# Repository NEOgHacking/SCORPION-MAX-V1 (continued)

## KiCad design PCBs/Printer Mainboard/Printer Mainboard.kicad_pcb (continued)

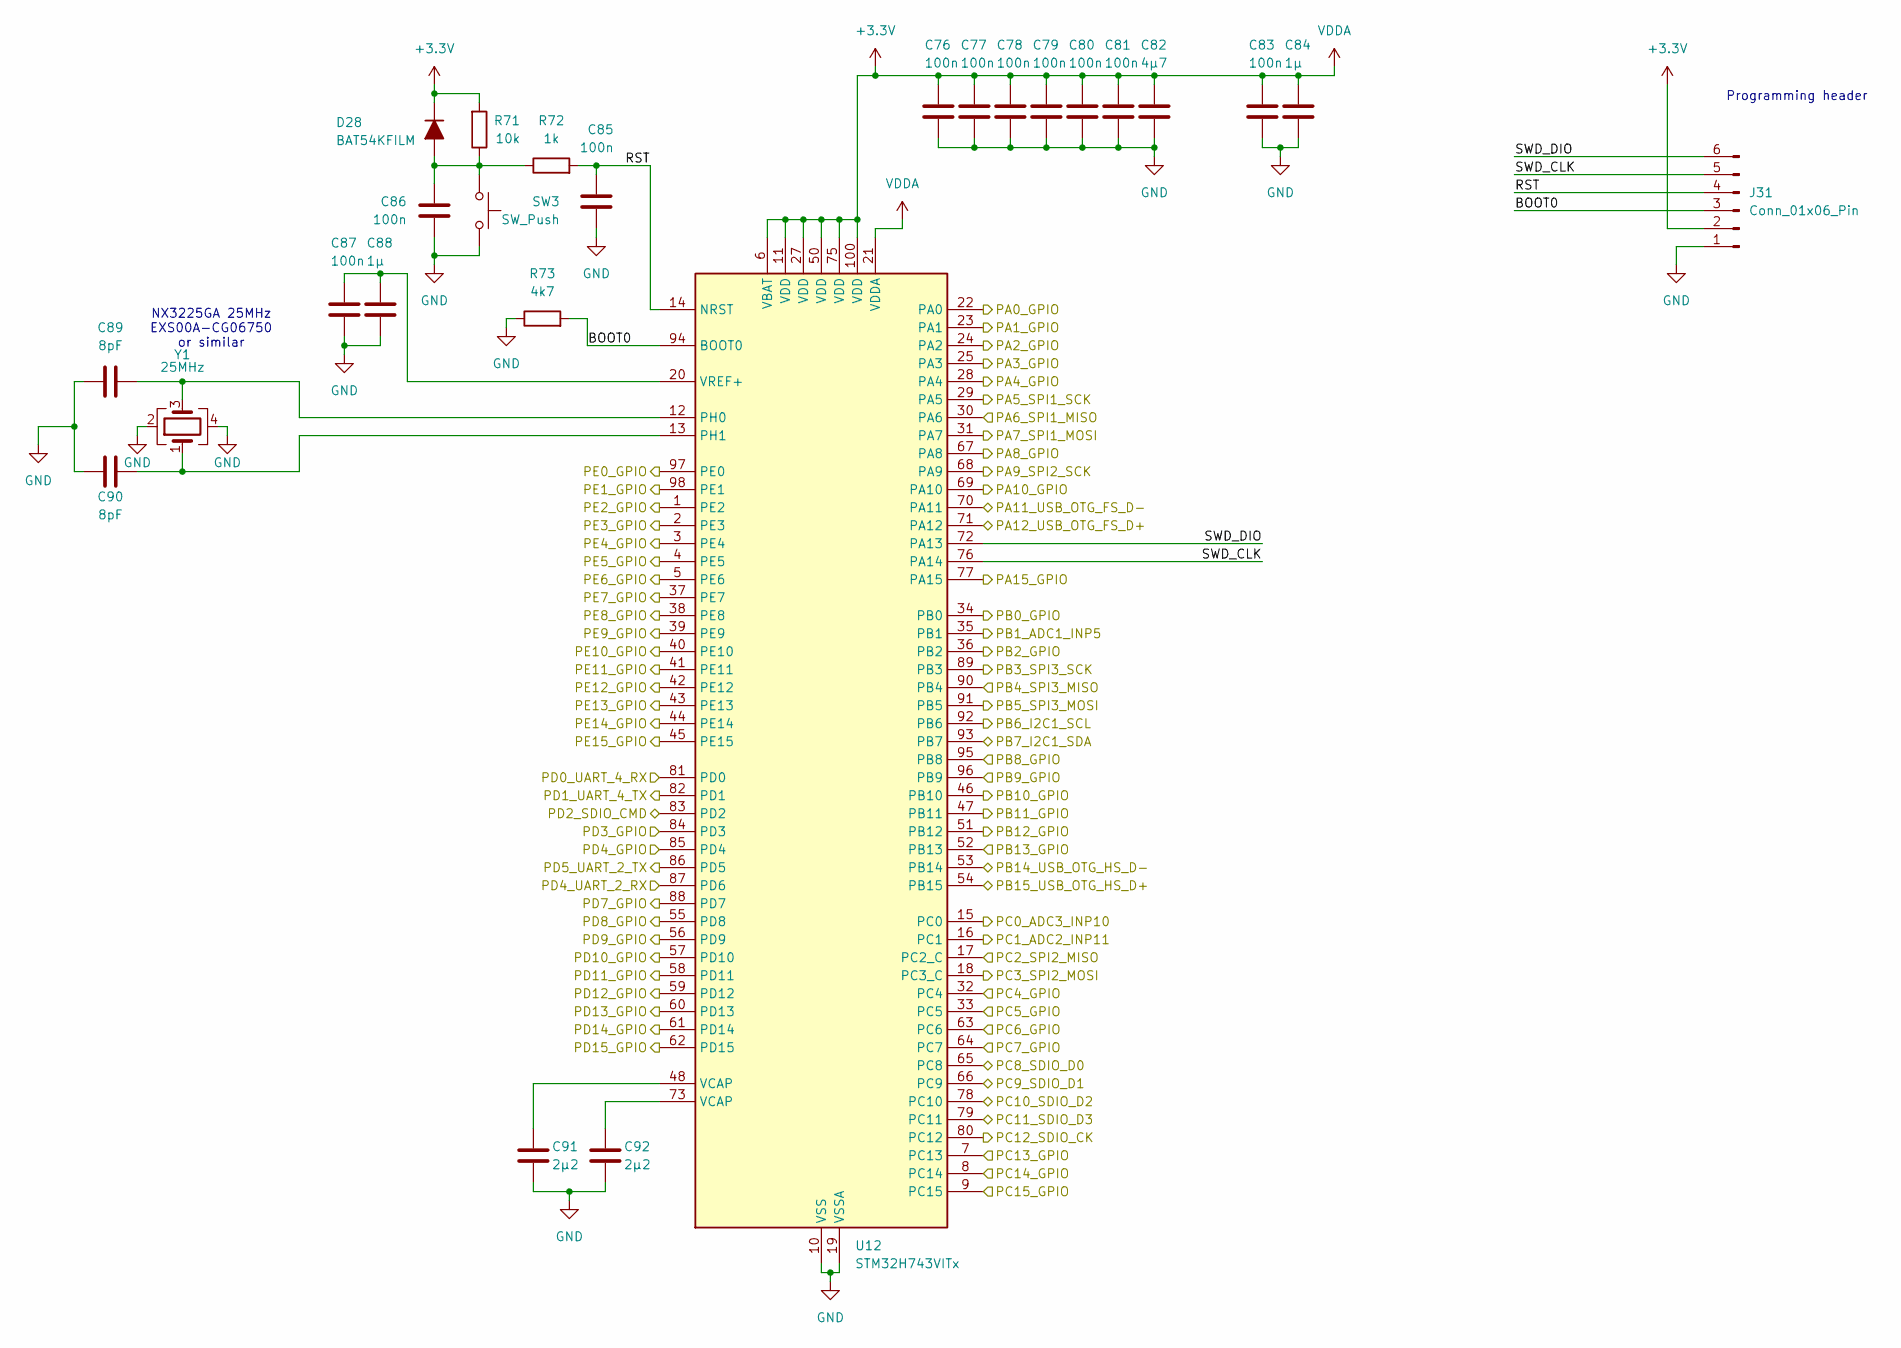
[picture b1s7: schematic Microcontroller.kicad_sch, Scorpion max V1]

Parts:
C76, C77, C78, C79, C80, C81, C83, C85, C86, C87: 100n; C_0603_1608Metric
C82: 4μ7; C_0805_2012Metric
C84, C88: 1μ; C_0603_1608Metric
C89, C90: 8pF; C_0603_1608Metric
C91, C92: 2μ2; C_0603_1608Metric
D28: BAT54KFILM; D_SOD-523
J31: Conn_01x06_Pin; PinHeader_1x06_P2.54mm_Vertical
R71: 10k; R_0603_1608Metric
R72: 1k; R_0603_1608Metric
R73: 4k7; R_0603_1608Metric
SW3: SW_Push; B3F3120
U12: STM32H743VITx; LQFP-100_14x14mm_P0.5mm
Y1: 25MHz; Crystal_SMD_3225-4Pin_3.2x2.5mm

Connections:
+3.3V: C76.1, C77.1, C78.1, C79.1, C80.1, C81.1, C82.1, C83.1, C84.1, D28.1 (K), J31.2, R71.2, U12.6 (VBAT), U12.11 (VDD), U12.21 (VDDA), U12.27 (VDD), U12.50 (VDD), U12.75 (VDD), U12.100 (VDD); also elsewhere on the board
/Expansion Port/GPIO_1: U12.5 (PE6); also elsewhere on the board
/Expansion Port/GPIO_2: U12.4 (PE5); also elsewhere on the board
/Expansion Port/GPIO_3: U12.3 (PE4); also elsewhere on the board
/Expansion Port/GPIO_4: U12.2 (PE3); also elsewhere on the board
/Expansion Port/GPIO_5: U12.1 (PE2); also elsewhere on the board
/Expansion Port/GPIO_6: U12.98 (PE1); also elsewhere on the board
/Expansion Port/GPIO_7: U12.97 (PE0); also elsewhere on the board
/Expansion Port/GPIO_8: U12.96 (PB9); also elsewhere on the board
/Expansion Port/GPIO_9: U12.84 (PD3); also elsewhere on the board
/Expansion Port/GPIO_10: U12.85 (PD4); also elsewhere on the board
/Expansion Port/GPIO_11: U12.88 (PD7); also elsewhere on the board
/Expansion Port/GPIO_12: U12.95 (PB8); also elsewhere on the board
/Expansion Port/RXD1: U12.81 (PD0); also elsewhere on the board
/Expansion Port/RXD2: U12.87 (PD6); also elsewhere on the board
/Expansion Port/SCL: U12.92 (PB6); also elsewhere on the board
/Expansion Port/SDA: U12.93 (PB7); also elsewhere on the board
/Expansion Port/SDIO_CK: U12.80 (PC12); also elsewhere on the board
/Expansion Port/SDIO_CMD: U12.83 (PD2); also elsewhere on the board
/Expansion Port/SDIO_D0: U12.65 (PC8); also elsewhere on the board
/Expansion Port/SDIO_D1: U12.66 (PC9); also elsewhere on the board
/Expansion Port/SDIO_D2: U12.78 (PC10); also elsewhere on the board
/Expansion Port/SDIO_D3: U12.79 (PC11); also elsewhere on the board
/Expansion Port/SPI_MISO: U12.90 (PB4); also elsewhere on the board
/Expansion Port/SPI_MOSI: U12.91 (PB5); also elsewhere on the board
/Expansion Port/SPI_SCK: U12.89 (PB3); also elsewhere on the board
/Expansion Port/TXD1: U12.82 (PD1); also elsewhere on the board
/Expansion Port/TXD2: U12.86 (PD5); also elsewhere on the board
/Fans Leds/FAN_1_PIN: U12.55 (PD8); also elsewhere on the board
/Fans Leds/FAN_1_TACH: U12.56 (PD9); also elsewhere on the board
/Fans Leds/FAN_2_PIN: U12.47 (PB11); also elsewhere on the board
/Fans Leds/FAN_2_TACH: U12.57 (PD10); also elsewhere on the board
/Fans Leds/FAN_3_PIN: U12.46 (PB10); also elsewhere on the board
/Fans Leds/FAN_3_TACH: U12.58 (PD11); also elsewhere on the board
/Fans Leds/FAN_4_PIN: U12.45 (PE15); also elsewhere on the board
/Fans Leds/FAN_4_TACH: U12.59 (PD12); also elsewhere on the board
/Limit Switches/LIMIT_1_PIN: U12.77 (PA15); also elsewhere on the board
/Limit Switches/LIMIT_2_PIN: U12.69 (PA10); also elsewhere on the board
/Limit Switches/LIMIT_3_PIN: U12.67 (PA8); also elsewhere on the board
/Limit Switches/LIMIT_4_PIN: U12.64 (PC7); also elsewhere on the board
/MOSFETS/MOSFET_1_PIN: U12.63 (PC6); also elsewhere on the board
/MOSFETS/MOSFET_2_PIN: U12.62 (PD15); also elsewhere on the board
/MOSFETS/MOSFET_3_PIN: U12.61 (PD14); also elsewhere on the board
/MOSFETS/MOSFET_4_PIN: U12.60 (PD13); also elsewhere on the board
/Microcontroller/BOOT0: J31.3, R73.2, U12.94 (BOOT0)
/Microcontroller/PA0_GPIO: U12.22 (PA0); also elsewhere on the board
/Microcontroller/PA1_GPIO: U12.23 (PA1); also elsewhere on the board
/Microcontroller/PA2_GPIO: U12.24 (PA2); also elsewhere on the board
/Microcontroller/PA3_GPIO: U12.25 (PA3); also elsewhere on the board
/Microcontroller/PA4_GPIO: U12.28 (PA4); also elsewhere on the board
/Microcontroller/PA5_SPI1_SCK: U12.29 (PA5); also elsewhere on the board
/Microcontroller/PA6_SPI1_MISO: U12.30 (PA6); also elsewhere on the board
/Microcontroller/PA7_SPI1_MOSI: U12.31 (PA7); also elsewhere on the board
/Microcontroller/PA9_SPI2_SCK: U12.68 (PA9); also elsewhere on the board
/Microcontroller/PB0_GPIO: U12.34 (PB0); also elsewhere on the board
/Microcontroller/PB1_ADC1_INP5: U12.35 (PB1); also elsewhere on the board
/Microcontroller/PB2_GPIO: U12.36 (PB2); also elsewhere on the board
/Microcontroller/PB12_GPIO: U12.51 (PB12); also elsewhere on the board
/Microcontroller/PB13_GPIO: U12.52 (PB13); also elsewhere on the board
/Microcontroller/PC0_ADC3_INP10: U12.15 (PC0); also elsewhere on the board
/Microcontroller/PC1_ADC2_INP11: U12.16 (PC1); also elsewhere on the board
/Microcontroller/PC2_SPI2_MISO: U12.17 (PC2_C); also elsewhere on the board
/Microcontroller/PC3_SPI2_MOSI: U12.18 (PC3_C); also elsewhere on the board
/Microcontroller/PC4_GPIO: U12.32 (PC4); also elsewhere on the board
/Microcontroller/PC5_GPIO: U12.33 (PC5); also elsewhere on the board
/Microcontroller/PC13_GPIO: U12.7 (PC13); also elsewhere on the board
/Microcontroller/PC14_GPIO: U12.8 (PC14); also elsewhere on the board
/Microcontroller/PC15_GPIO: U12.9 (PC15); also elsewhere on the board
/Microcontroller/PE7_GPIO: U12.37 (PE7); also elsewhere on the board
/Microcontroller/PE8_GPIO: U12.38 (PE8); also elsewhere on the board
/Microcontroller/PE9_GPIO: U12.39 (PE9); also elsewhere on the board
/Microcontroller/PE10_GPIO: U12.40 (PE10); also elsewhere on the board
/Microcontroller/PE11_GPIO: U12.41 (PE11); also elsewhere on the board
/Microcontroller/PE12_GPIO: U12.42 (PE12); also elsewhere on the board
/Microcontroller/PE13_GPIO: U12.43 (PE13); also elsewhere on the board
/Microcontroller/PE14_GPIO: U12.44 (PE14); also elsewhere on the board
/Microcontroller/RST: C85.1, J31.4, R72.2, U12.14 (NRST)
/Microcontroller/SWD_CLK: J31.5, U12.76 (PA14)
/Microcontroller/SWD_DIO: J31.6, U12.72 (PA13)
/USB/USB_A_D+: U12.54 (PB15); also elsewhere on the board
/USB/USB_A_D-: U12.53 (PB14); also elsewhere on the board
/USB/USB_C_D+: U12.71 (PA12); also elsewhere on the board
/USB/USB_C_D-: U12.70 (PA11); also elsewhere on the board
GND: C76.2, C77.2, C78.2, C79.2, C80.2, C81.2, C82.2, C83.2, C84.2, C85.2, C86.2, C87.2, C88.2, C89.1, C90.1, C91.2, C92.2, J31.1, R73.1, SW3.1, U12.10 (VSS), U12.19 (VSSA), U12.26 (VSS), U12.49 (VSS), U12.74 (VSS), U12.99 (VSS), Y1.2, Y1.4; also elsewhere on the board
unnamed: C91.1, U12.48 (VCAP)
unnamed: C92.1, U12.73 (VCAP)
unnamed: C86.1, D28.2 (A), R71.1, R72.1, SW3.2
unnamed: C89.2, U12.12 (PH0), Y1.3
unnamed: C90.2, U12.13 (PH1), Y1.1
unnamed: C87.1, C88.1, U12.20 (VREF+)

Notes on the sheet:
Programming header
NX3225GA 25MHz EXS00A-CG06750 or similar

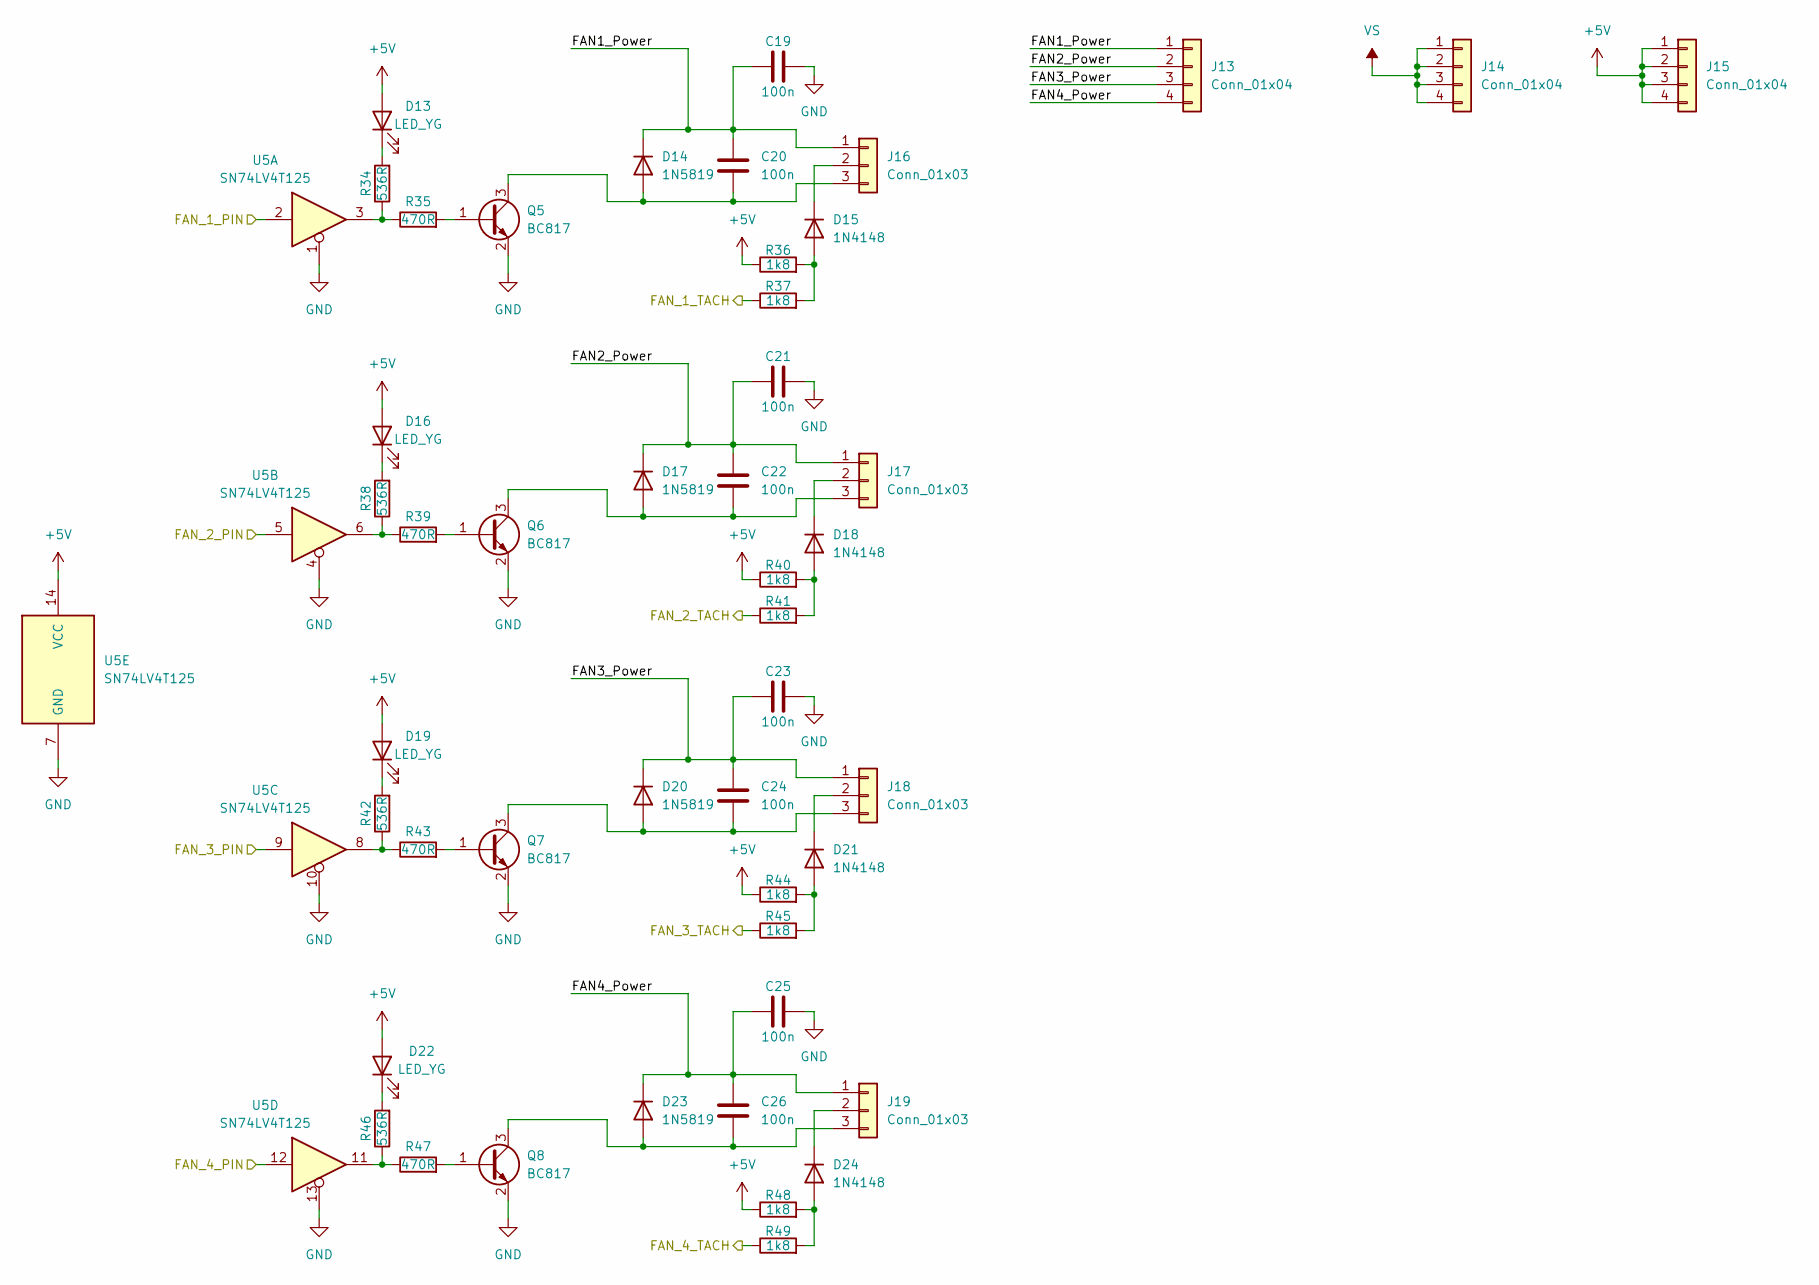
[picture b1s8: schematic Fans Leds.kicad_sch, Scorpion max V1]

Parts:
C19, C20, C21, C22, C23, C24, C25, C26: 100n; C_0603_1608Metric
D13, D16, D19, D22: LED_YG; LED_0603_1608Metric
D14, D17, D20, D23: 1N5819; D_SOD-323
D15, D18, D21, D24: 1N4148; D_SOD-523
J13, J14, J15: Conn_01x04; PinSocket_1x04_P2.54mm_Vertical
J16, J17, J18, J19: Conn_01x03; JST_XH_B3B-XH-A_1x03_P2.50mm_Vertical
Q5, Q6, Q7, Q8: BC817; SOT-23
R34, R38, R42, R46: 536R; R_0603_1608Metric
R35, R39, R43, R47: 470R; R_0603_1608Metric
R36, R37, R40, R41, R44, R45, R48, R49: 1k8; R_0603_1608Metric
U5: SN74LV4T125; TSSOP-14_4.4x5mm_P0.65mm

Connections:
+5V: D13.2 (A), D16.2 (A), D19.2 (A), D22.2 (A), J15.1, J15.2, J15.3, J15.4, R36.1, R40.1, R44.1, R48.1, U5.14 (VCC); also elsewhere on the board
/Fans Leds/FAN1_Power: C19.1, C20.1, D14.1 (K), J13.1, J16.1
/Fans Leds/FAN2_Power: C21.1, C22.1, D17.1 (K), J13.2, J17.1
/Fans Leds/FAN3_Power: C23.1, C24.1, D20.1 (K), J13.3, J18.1
/Fans Leds/FAN4_Power: C25.1, C26.1, D23.1 (K), J13.4, J19.1
/Fans Leds/FAN_1_PIN: U5.2; also elsewhere on the board
/Fans Leds/FAN_1_TACH: R37.1; also elsewhere on the board
/Fans Leds/FAN_2_PIN: U5.5; also elsewhere on the board
/Fans Leds/FAN_2_TACH: R41.1; also elsewhere on the board
/Fans Leds/FAN_3_PIN: U5.9; also elsewhere on the board
/Fans Leds/FAN_3_TACH: R45.1; also elsewhere on the board
/Fans Leds/FAN_4_PIN: U5.12; also elsewhere on the board
/Fans Leds/FAN_4_TACH: R49.1; also elsewhere on the board
GND: C19.2, C21.2, C23.2, C25.2, Q5.2 (E), Q6.2 (E), Q7.2 (E), Q8.2 (E), U5.1, U5.4, U5.7 (GND), U5.10, U5.13; also elsewhere on the board
unnamed: D13.1 (K), R34.2
unnamed: C20.2, D14.2 (A), J16.3, Q5.3 (C)
unnamed: D15.2 (A), R36.2, R37.2
unnamed: D15.1 (K), J16.2
unnamed: D16.1 (K), R38.2
unnamed: C22.2, D17.2 (A), J17.3, Q6.3 (C)
unnamed: D18.2 (A), R40.2, R41.2
unnamed: D18.1 (K), J17.2
unnamed: D19.1 (K), R42.2
unnamed: C24.2, D20.2 (A), J18.3, Q7.3 (C)
unnamed: D21.2 (A), R44.2, R45.2
unnamed: D21.1 (K), J18.2
unnamed: D22.1 (K), R46.2
unnamed: C26.2, D23.2 (A), J19.3, Q8.3 (C)
unnamed: D24.2 (A), R48.2, R49.2
unnamed: D24.1 (K), J19.2
unnamed: Q5.1 (B), R35.2
unnamed: Q6.1 (B), R39.2
unnamed: Q7.1 (B), R43.2
unnamed: Q8.1 (B), R47.2
unnamed: R34.1, R35.1, U5.3
unnamed: R38.1, R39.1, U5.6
unnamed: R42.1, R43.1, U5.8
unnamed: R46.1, R47.1, U5.11
VS: J14.1, J14.2, J14.3, J14.4; also elsewhere on the board

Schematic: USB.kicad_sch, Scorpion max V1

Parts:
C1: 100n; C_0603_1608Metric
C2: 4μ7; C_0805_2012Metric
D1: LED_R; LED_0603_1608Metric
D2: DSK24L; D_SOD-123F
J1: USB_A; USB-A-TH_USB-302-T
J2: USB_C_Receptacle_USB2.0_14P; USB-C_SMD-TYPE-C-31-M-12_1
R1: 47k; R_0603_1608Metric
R2: 620R; R_0603_1608Metric
R3, R4: 5k1; R_0603_1608Metric
S1: STMPS2141STR; SOT95P280X145-5N; Mouser Part Number 511-STMPS2141STR
U1: USBLC6-2SC6; SOT-23-6

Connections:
+5V: D2.1 (K), R1.1, R2.1, S1.5 (IN); also elsewhere on the board
/Microcontroller/PB12_GPIO: S1.4 (EN); also elsewhere on the board
/Microcontroller/PB13_GPIO: D1.1 (K), R1.2, S1.3 (FAULT); also elsewhere on the board
/USB/USB_A_D+: U1.1 (I/O1); also elsewhere on the board
/USB/USB_A_D-: U1.3 (I/O2); also elsewhere on the board
/USB/USB_A_VBUS: C1.1, C2.1, J1.1 (VBUS), S1.1 (OUT), U1.5 (VBUS)
/USB/USB_C_D+: J2.A6 (D+), J2.B6 (D+); also elsewhere on the board
/USB/USB_C_D-: J2.A7 (D-), J2.B7 (D-); also elsewhere on the board
GND: C1.2, C2.2, J1.4 (GND), J1.5 (Shield), J2.A1B12 (GND), J2.B1A12 (GND), J2.S1 (SHIELD), R3.2, R4.2, S1.2 (GND), U1.2 (GND); also elsewhere on the board
unnamed: D1.2 (A), R2.2
unnamed: D2.2 (A), J2.A4B9 (VBUS), J2.B4A9 (VBUS)
unnamed: J1.3 (D+), U1.6 (I/O1)
unnamed: J1.2 (D-), U1.4 (I/O2)
unnamed: J2.A5 (CC1), R3.1
unnamed: J2.B5 (CC2), R4.1

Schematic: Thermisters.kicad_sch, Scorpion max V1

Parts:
C93, C94, C95: 100n; C_0603_1608Metric
J32, J35, J38: Conn_01x03; PinSocket_1x03_P2.54mm_Vertical
J33, J36, J39: Conn_01x02; JST_XH_B2B-XH-A_1x02_P2.50mm_Vertical
J34, J37, J40: Conn_01x02; PinSocket_1x02_P2.54mm_Vertical

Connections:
+3.3V: J32.3, J35.3, J38.3; also elsewhere on the board
/Microcontroller/PB1_ADC1_INP5: C93.1, J32.2; also elsewhere on the board
/Microcontroller/PC0_ADC3_INP10: C95.1, J38.2; also elsewhere on the board
/Microcontroller/PC1_ADC2_INP11: C94.1, J35.2; also elsewhere on the board
GND: C93.2, C94.2, C95.2, J32.1, J35.1, J38.1; also elsewhere on the board
unnamed: J33.1, J34.1
unnamed: J33.2, J34.2
unnamed: J36.1, J37.1
unnamed: J36.2, J37.2
unnamed: J39.1, J40.1
unnamed: J39.2, J40.2

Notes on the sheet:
Thermister
Temp Module

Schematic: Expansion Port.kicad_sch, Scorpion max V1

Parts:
J11, J12: Conn_02x08_Odd_Even; PinSocket_2x08_P2.54mm_Vertical

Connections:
+3.3V: J11.14; also elsewhere on the board
+5V: J11.16, J12.16; also elsewhere on the board
/Expansion Port/GPIO_1: J12.1; also elsewhere on the board
/Expansion Port/GPIO_2: J12.2; also elsewhere on the board
/Expansion Port/GPIO_3: J12.3; also elsewhere on the board
/Expansion Port/GPIO_4: J12.4; also elsewhere on the board
/Expansion Port/GPIO_5: J12.5; also elsewhere on the board
/Expansion Port/GPIO_6: J12.6; also elsewhere on the board
/Expansion Port/GPIO_7: J12.7; also elsewhere on the board
/Expansion Port/GPIO_8: J12.8; also elsewhere on the board
/Expansion Port/GPIO_9: J12.9; also elsewhere on the board
/Expansion Port/GPIO_10: J12.10; also elsewhere on the board
/Expansion Port/GPIO_11: J12.11; also elsewhere on the board
/Expansion Port/GPIO_12: J12.12; also elsewhere on the board
/Expansion Port/RXD1: J11.6; also elsewhere on the board
/Expansion Port/RXD2: J11.10; also elsewhere on the board
/Expansion Port/SCL: J12.14; also elsewhere on the board
/Expansion Port/SDA: J12.13; also elsewhere on the board
/Expansion Port/SDIO_CK: J11.5; also elsewhere on the board
/Expansion Port/SDIO_CMD: J11.8; also elsewhere on the board
/Expansion Port/SDIO_D0: J11.1; also elsewhere on the board
/Expansion Port/SDIO_D1: J11.2; also elsewhere on the board
/Expansion Port/SDIO_D2: J11.3; also elsewhere on the board
/Expansion Port/SDIO_D3: J11.4; also elsewhere on the board
/Expansion Port/SPI_MISO: J11.12; also elsewhere on the board
/Expansion Port/SPI_MOSI: J11.13; also elsewhere on the board
/Expansion Port/SPI_SCK: J11.11; also elsewhere on the board
/Expansion Port/TXD1: J11.7; also elsewhere on the board
/Expansion Port/TXD2: J11.9; also elsewhere on the board
GND: J11.15, J12.15; also elsewhere on the board

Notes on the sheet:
Expansion Module

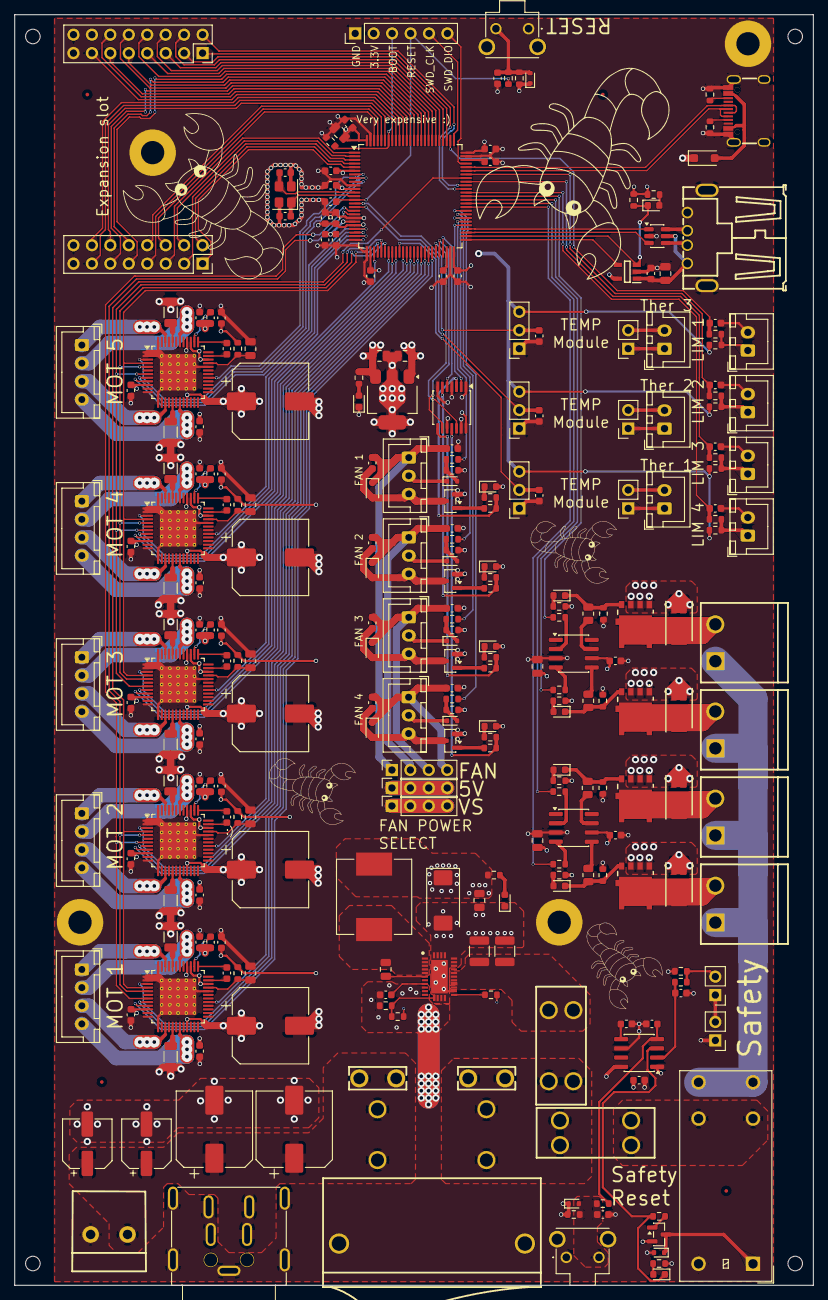
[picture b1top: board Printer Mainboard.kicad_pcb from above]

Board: 4 copper layers, 110.0 x 175.0 mm, 279 parts (0 on the bottom side), 228 nets.

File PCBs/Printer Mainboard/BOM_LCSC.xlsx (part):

Reference | Qty | Value | DNP | Exclude from BOM | Exclude from Board | Footprint | Part | component | LCSC number | Qty 2x Boards | Order | Total Price | Do Not Order | Extra
C1,C11,C12,C13,C14,C16,C18,C19,C20,C21,C22,C23,C24,C25,C26,C31,C32,C33,C34,C46,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 | 52 | 100n | 1 |  |  | Capacitor_SMD:C_0603_1608Metric | Capacitor 100n 50V | CC0603KRX7R9BB104 | C14663 | 104 | 200 | 0.44 |  |  |  |  |  |  |  |  |  |  |  |  | Vin | Vmin | Vmax | Vavg. | mA | R
C2,C9,C10,C15,C17,C41,C42,C43,C44,C45,C82 | 11 | 4Î¼7 | 2 |  |  | Capacitor_SMD:C_0805_2012Metric | Capacitor 4μ7 50V | CL21A475KBQNNNE | C98192 | 22 | 50 | 0.88 |  |  |  |  |  |  |  |  |  |  |  | Led Red | 3.3 | 1.6 | 2.1 | 1.85 | 5 | 289.99999999999994
C3,C5 | 2 | 470n 10V | 3 |  |  | Capacitor_SMD:C_0805_2012Metric | Capacitor 470n 10V | VJ0805Y474KXQTW1BC | C2177586 | 4 | 5 | 0.26 |  |  |  |  |  |  |  |  |  |  |  | Led Blue | 3.3 | 2.6 | 3.2 | 2.9000000000000004 | 5 | 79.999999999999886
C4 | 1 | 220Î¼ 10V | 4 |  |  | Capacitor_Tantalum_SMD:CP_EIA-7343-43_Kemet-X | Capacitor 220μ 10V | 593D227X0010E2TE3 | C1952898 | 2 | 2 | 0.85 |  |  |  |  |  |  |  |  |  |  |  | Led Green | 3.3 | 2.4 | 3 | 2.7 | 5 | 119.99999999999993
C6 | 1 | 470n 100V | 5 |  |  | Capacitor_SMD:C_1210_3225Metric | Capacitor 470n 100V | VJ1210Y474KXBAT | C2313088 | 2 | 3 | 1.28 |  |  |  |  |  |  |  |  |  |  |  | Led Yellow Green | 3.3 | 2.2999999999999998 | 2.2999999999999998 | 2.2999999999999998 | 5 | 200
C7 | 1 | 4Î¼7 100V | 6 |  |  | Capacitor_SMD:C_1210_3225Metric | Capacitor 4μ7 100V | C3225X7S2A475KT003S | C694475 | 2 | 5 | 1.97 |  |  |  |  |  |  |  |  |  |  |  | Led Red | 5 | 1.6 | 2.1 | 1.85 | 5 | 630
C8 | 1 | 2Î¼2 16V | 7 |  |  | Capacitor_SMD:C_0603_1608Metric | Capacitor 2μ2 16V | C1608X5R1C225KT000N | C76612 | 2 | 5 | 0.16 |  |  |  |  |  |  |  |  |  |  |  | Led Blue | 5 | 2.6 | 3.2 | 2.9000000000000004 | 5 | 419.99999999999994
C27,C28,C48,C51,C54,C57,C60 | 7 | 100Î¼ | 8 |  |  | Capacitor_SMD:CP_Elec_10x10 | Capacitor 100μ 63V | RVT1J101M1010 | C72481 | 14 | 20 | 1.75 |  |  |  |  |  |  |  |  |  |  |  | Led Green | 5 | 2.4 | 3 | 2.7 | 5 | 459.99999999999994
C29,C30 | 2 | 10Î¼ | 9 |  |  | Capacitor_SMD:CP_Elec_6.3x5.8 | Capacitor 10μ 63V | EEEFK1J100P | C128459 | 4 | 5 | 0.64 |  |  |  |  |  |  |  |  |  |  |  | Led Yellow Green | 5 | 2.2999999999999998 | 2.2999999999999998 | 2.2999999999999998 | 5 | 540
C35 | 1 | 10n | 10 |  |  | Capacitor_SMD:C_0603_1608Metric | Capacitor 10n 50V | CC0603KRX7R9BB103 | C100042 | 2 | 100 | 0.2
C36,C37,C38,C39,C40 | 5 | 470n | 11 |  |  | Capacitor_SMD:C_0603_1608Metric | Capacitor 470n 50V | CC0603KRX7R9BB474 | C513577 | 10 | 50 | 0.38
C71,C72,C73,C74,C75 | 5 | 22n | 12 |  |  | Capacitor_SMD:C_0603_1608Metric | Capacitor 22n 50V | CC0603KRX7R9BB223 | C106222 | 10 | 100 | 0.27
C84,C88 | 2 | 1Î¼ | 13 |  |  | Capacitor_SMD:C_0603_1608Metric | Capacitor 1μ 50V | CL10A105KB8NNNC | C15849 | 4 | 50 | 0.22
C89,C90 | 2 | 8pF | 14 |  |  | Capacitor_SMD:C_0603_1608Metric | Capacitor 8p 50V | CL10C080DB81PNC | C346204 | 4 | 50 | 0.44
C91,C92 | 2 | 2Î¼2 | 15 |  |  | Capacitor_SMD:C_0603_1608Metric | Capacitor 2μ2 50V | CL10A225KB8NNNC | C913904 | 4 | 50 | 0.96
D1,D26 | 2 | LED_R | 16 |  |  | LED_SMD:LED_0603_1608Metric | Led Red | A-SP192XR5C-A01-4T | C19171307 | 4 | 20 | 0.38
D2 | 1 | DSK24L | 17 |  |  | Diode_SMD:D_SOD-123F | Diode Low Forward Voltage | DSK24L | C19272974 | 2 | 10 | 0.5
D3,D4 | 2 | LED_G | 18 |  |  | LED_SMD:LED_0603_1608Metric | Led Green | A-SP192DGHC-C01-4T | C19171301 | 4 | 20 | 0.56000000000000005
D5,D7,D9,D11 | 4 | SMBJ64A | 19 |  |  | SamacSys_Parts:DIOM5436X250N | Diode Clamp | SMBJ64A | C19077594 | 8 | 10 | 0.4
D6,D8,D10,D12 | 4 | LED_B | 20 |  |  | LED_SMD:LED_0603_1608Metric | Led Blue | A-SP192DB1C-C01-4T | C5355419 | 8 | 20 | 0.44
D13,D16,D19,D22 | 4 | LED_YG | 21 |  |  | LED_SMD:LED_0603_1608Metric | Led Yellow Green | A-SP192DG2C-C01-4T | C5151486 | 8 | 20 | 0.56999999999999995
D14,D17,D20,D23 | 4 | 1N5819 | 22 |  |  | Diode_SMD:D_SOD-323 | Diode Schottky | 1N5819WS | C191023 | 8 | 50 | 0.47
D15,D18,D21,D24,D27 | 5 | 1N4148 | 23 |  |  | Diode_SMD:D_SOD-523 | Diode | 1N4148WT | C917006 | 10 | 100 | 0.44
D25,D28 | 2 | BAT54KFILM | 24 |  |  | Diode_SMD:D_SOD-523 | Diode Schottky | BAT54KFILM | C283259 | 4 | 10 | 0.5
F1,F2 | 2 | XF-508P-B-B | 25 |  |  | LCSC:FUSE-TH_4P-L16.0-W6.7 | Fuse Holder | XF-508P-B-B | C19727305 | 4 | 5 | 0.59
IC1 | 1 | LM76005RNPR | 26 |  |  | SamacSys_Parts:QFN50P400X600X80-31N-D | DC/DC Converter IC | LM76005QRNPRQ1 | C2873394 | 2 | 5 | 1
J1 | 1 | USB_A | 27 |  |  | LCSC:USB-A-TH_USB-302-T | USB_A | USB-302-T | C112456 | 2 | 2 | 9.7100000000000009
J2 | 1 | USB_C_Receptacle_USB2.0_14P | 28 |  |  | LCSC:USB-C_SMD-TYPE-C-31-M-12_1 | USB_C | TYPE-C-31-M-12 | C165948 | 2 | 5 | 0.77
J3,J4,J5,J6,J33,J36,J39 | 7 | Conn_01x02 | 29 |  |  | Connector_JST:JST_XH_B2B-XH-A_1x02_P2.50mm_Vertical | 2 Pin JST_XH | B2B-XH-A(LF)(SN) | C158012 | 14 | 20 | 0.61
J7,J8,J9,J10 | 4 | Conn_01x02 | 30 |  |  | LCSC:CONN-TH_2P-P5.08_2EDG-5.08-2AW | 2 Pin Header | 1923869 | C5443585 | 8 | 10 | 4.34 | x | I have these at home
J11,J12 | 2 | Conn_02x08_Odd_Even | 31 |  |  | Connector_PinSocket_2.54mm:PinSocket_2x08_P2.54mm_Vertical | 2x8 Pin Socket | PM2.54-2X8PM-H85 | C42431844 | 4 | 10 | 0.37
J13,J14,J15 | 3 | Conn_01x04 | 32 |  |  | Connector_PinSocket_2.54mm:PinSocket_1x04_P2.54mm_Vertical | 1x4 Pin Socket | PM2.54-1X4PM-H85 | C42431839 | 6 | 10 | 0.34
J16,J17,J18,J19 | 4 | Conn_01x03 | 33 |  |  | Connector_JST:JST_XH_B3B-XH-A_1x03_P2.50mm_Vertical | 3 Pin JST_XH | B3B-XH-A(LF)(SN) | C144394 | 8 | 10 | 0.41
J20,J21 | 2 | Faston | 34 |  |  | LCSC:CONN-TH_63849-1 | Faston | 63849-1 | C86469 | 4 | 10 | 0.54
J22 | 1 | Mini-DIN-4 | 35 |  |  | LCSC:CONN-TH_DIN-422 | 4 Pin Power In Connector | DIN-422 | C2939341 | 2 | 5 | 1.31
J23 | 1 | Conn_01x02 | 36 |  |  | LCSC:CONN-TH_MKDS3-2-5.08 | 2 Pin Screw Terminal | 1711725 | C89120 | 2 | 2 | 1.79
J24,J25 | 2 | Conn_01x02 | 37 |  |  | Connector_PinHeader_2.54mm:PinHeader_1x02_P2.54mm_Vertical | 1x2 Pin Header | PH2.54-1X2P-H25 | C42431798 | 4 | 50 | 0.33
J26,J27,J28,J29,J30 | 5 | Conn_01x04 | 38 |  |  | Connector_JST:JST_XH_B4B-XH-A_1x04_P2.50mm_Vertical | 4 Pin JST_XH | B4B-XH-A(LF)(SN) | C144395 | 10 | 20 | 0.89
J31 | 1 | Conn_01x06_Pin | 39 |  |  | Connector_PinHeader_2.54mm:PinHeader_1x06_P2.54mm_Vertical | 1x6 Pin Header | PZ2.54-1X6P-H25 | C42431790 | 2 | 20 | 0.25
J32,J35,J38 | 3 | Conn_01x03 | 40 |  |  | Connector_PinSocket_2.54mm:PinSocket_1x03_P2.54mm_Vertical | 1x3 Pin Socket | PM2.54-1X3P-H85 | C42431866 | 6 | 10 | 0.34
J34,J37,J40 | 3 | Conn_01x02 | 41 |  |  | Connector_PinSocket_2.54mm:PinSocket_1x02_P2.54mm_Vertical | 1x2 Pin Socket | PM2.54-1X2PM-H85 | C42431841 | 6 | 10 | 0.7
K1 | 1 | G2RL-1A-E | 42 |  |  | Relay_THT:Relay_SPST_Omron_G2RL-1A-E | Relay | G2RL-1A-E DC5 | C397259 | 2 | 2 | 2.73
L1 | 1 | 6.8Î¼ | 43 |  |  | Inductor_SMD:L_Vishay_IHLP-4040 | Inductor | IHLP4040DZER6R8M01 | C845080 | 2 | 2 | 1.66
Q1,Q2,Q3,Q4 | 4 | NVMFWS4D5N08XT1G | 44 |  |  | SamacSys_Parts:NVMFS5C460NWFT1G | Mosfet | NVMFWS4D5N08XT1G | C29841638 | 8 | 10 | 15.58
Q5,Q6,Q7,Q8 | 4 | BC817 | 45 |  |  | Package_TO_SOT_SMD:SOT-23 | Transistor NPN | BC817-40,215 | C52801 | 8 | 20 | 0.48
Q9 | 1 | BC807 | 46 |  |  | Package_TO_SOT_SMD:SOT-23 | Transistor PNP | BC807-40,215 | C57316 | 2 | 20 | 0.6
R1 | 1 | 47k | 47 |  |  | Resistor_SMD:R_0603_1608Metric | Resistor 47k | RC0603FR-0747KL | C105579 | 2 | 100 | 0.12
R2 | 1 | 620R | 48 |  |  | Resistor_SMD:R_0603_1608Metric | Resistor 620R | RC0603FR-07620RL | C137695 | 2 | 100 | 0.12
R3,R4 | 2 | 5k1 | 49 |  |  | Resistor_SMD:R_0603_1608Metric | Resistor 5k1 | RC0603FR-075K1L | C105580 | 4 | 100 | 0.13
R5 | 1 | 120R | 50 |  |  | Resistor_SMD:R_0603_1608Metric | Resisitor 120R | RC0603FR-07120RL | C114640 | 2 | 100 | 0.13
R6,R35,R39,R43,R47,R54 | 6 | 470R | 51 |  |  | Resistor_SMD:R_0603_1608Metric | Resistor 470R | RC0603FR-07470RL | C114669 | 12 | 100 | 0.13
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
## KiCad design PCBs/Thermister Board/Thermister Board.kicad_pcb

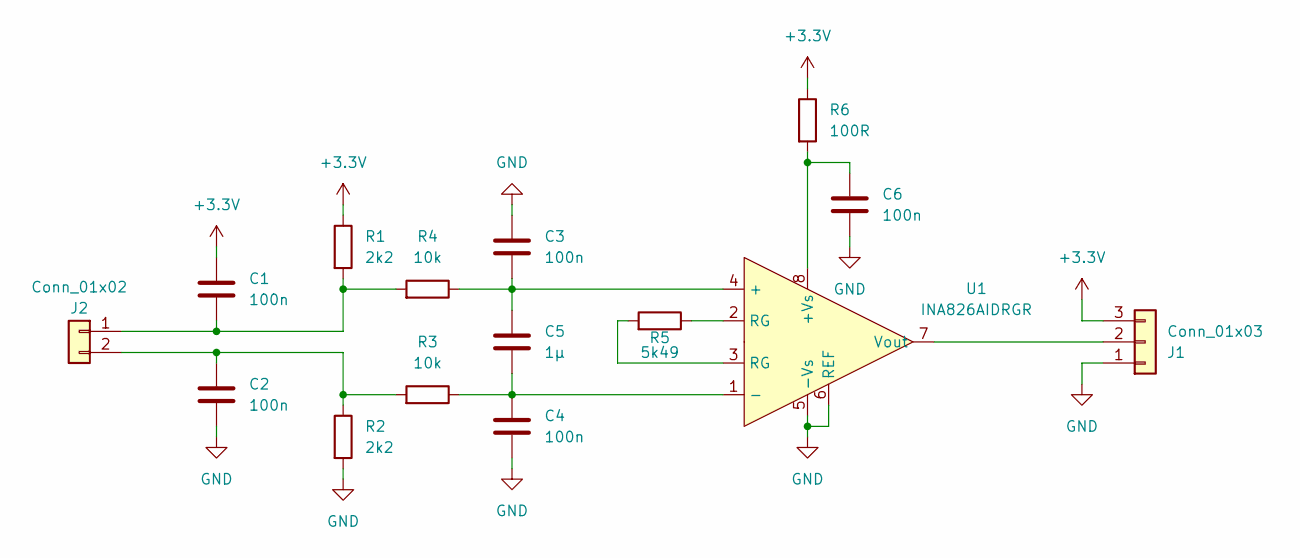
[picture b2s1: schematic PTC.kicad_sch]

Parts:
C1, C2, C3, C4, C6: 100n; C_0603_1608Metric
C5: 1µ; C_0603_1608Metric
J1: Conn_01x03; PinHeader_1x03_P2.54mm_Vertical
J2: Conn_01x02; PinHeader_1x02_P2.54mm_Vertical
R1, R2: 2k2; R_0603_1608Metric
R3, R4: 10k; R_0603_1608Metric
R5: 5k49; R_0603_1608Metric
R6: 100R; R_0603_1608Metric
U1: INA826AIDRGR; WSON-8-1EP_3x3mm_P0.5mm_EP1.45x2.4mm_ThermalVias

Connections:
+3.3V: C1.1, J1.3, R1.1, R6.1; also elsewhere on the board
GND: C2.2, C3.1, C4.2, C6.2, J1.1, R2.2, U1.5 (-Vs), U1.6 (REF); also elsewhere on the board
unnamed: C4.1, C5.2, R3.1, U1.1 (-), U1.9 (-)
unnamed: J1.2, U1.7 (Vout)
unnamed: C1.2, J2.1, R1.2, R4.2
unnamed: C2.1, J2.2, R2.1, R3.2
unnamed: R5.1, U1.2 (RG)
unnamed: R5.2, U1.3 (RG)
unnamed: C3.2, C5.1, R4.1, U1.4 (+)
unnamed: C6.1, R6.2, U1.8 (+Vs)

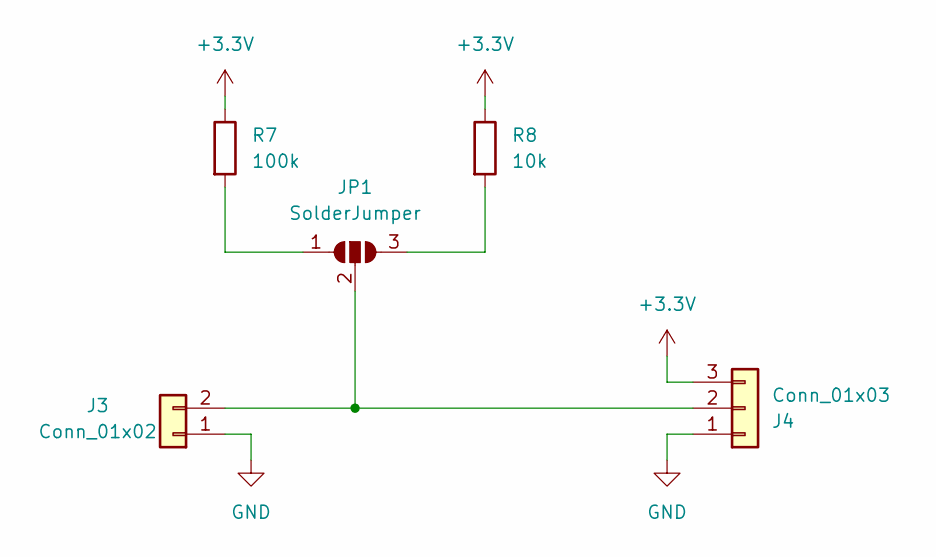
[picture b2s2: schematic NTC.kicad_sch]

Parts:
J3: Conn_01x02; PinHeader_1x02_P2.54mm_Vertical
J4: Conn_01x03; PinHeader_1x03_P2.54mm_Vertical
JP1: SolderJumper; SolderJumper-3_P1.3mm_Open_RoundedPad1.0x1.5mm_NumberLabels
R7: 100k; R_0603_1608Metric
R8: 10k; R_0603_1608Metric

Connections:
+3.3V: J4.3, R7.1, R8.1; also elsewhere on the board
GND: J3.1, J4.1; also elsewhere on the board
unnamed: J3.2, J4.2, JP1.2 (C)
unnamed: JP1.1 (A), R7.2
unnamed: JP1.3 (B), R8.2

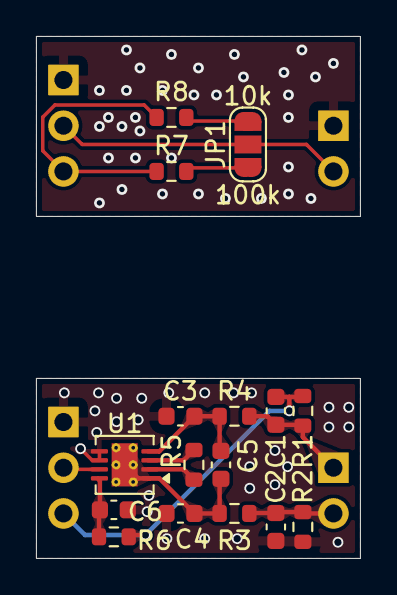
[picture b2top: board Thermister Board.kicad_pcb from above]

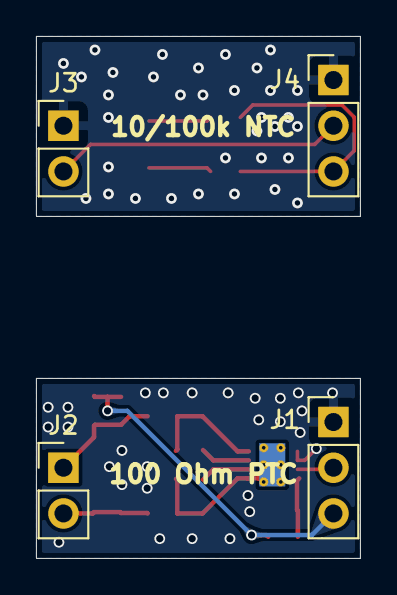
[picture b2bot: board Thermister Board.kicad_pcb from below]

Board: 2 copper layers, 18.0 x 29.0 mm, 20 parts (4 on the bottom side), 13 nets.

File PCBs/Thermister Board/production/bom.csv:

Designator,Footprint,Quantity,Value,LCSC Part #
"C1_12, C1_11, C1_10, C1_9, C1_8, C1_7, C1_6, C1_5, C1_4, C1_3, C1_2, C1, C2_12, C2_11, C2_10, C2_9, C2_8, C2_7, C2_6, C2_5, C2_4, C2_3, C2_2, C2, C3_12, C3_11, C3_10, C3_9, C3_8, C3_7, C3_6, C3_5, C3_4, C3_3, C3_2, C3, C4_12, C4_11, C4_10, C4_9, C4_8, C4_7, C4_6, C4_5, C4_4, C4_3, C4_2, C4, C6_12, C6_11, C6_10, C6_9, C6_8, C6_7, C6_6, C6_5, C6_4, C6_3, C6_2, C6",0603,60,100n,
"C5_12, C5_11, C5_10, C5_9, C5_8, C5_7, C5_6, C5_5, C5_4, C5_3, C5_2, C5",0603,12,1µ,
"J1_12, J1_11, J1_10, J1_9, J1_8, J1_7, J1_6, J1_5, J1_4, J1_3, J1_2, J1, J4_12, J4_11, J4_10, J4_9, J4_8, J4_7, J4_6, J4_5, J4_4, J4_3, J4_2, J4",PinHeader_1x03_P2.54mm_Vertical,24,Conn_01x03,
"J2_12, J2_11, J2_10, J2_9, J2_8, J2_7, J2_6, J2_5, J2_4, J2_3, J2_2, J2, J3_12, J3_11, J3_10, J3_9, J3_8, J3_7, J3_6, J3_5, J3_4, J3_3, J3_2, J3",PinHeader_1x02_P2.54mm_Vertical,24,Conn_01x02,
"R1_12, R1_11, R1_10, R1_9, R1_8, R1_7, R1_6, R1_5, R1_4, R1_3, R1_2, R1, R2_12, R2_11, R2_10, R2_9, R2_8, R2_7, R2_6, R2_5, R2_4, R2_3, R2_2, R2",0603,24,2k2,
"R3_12, R3_11, R3_10, R3_9, R3_8, R3_7, R3_6, R3_5, R3_4, R3_3, R3_2, R3, R4_12, R4_11, R4_10, R4_9, R4_8, R4_7, R4_6, R4_5, R4_4, R4_3, R4_2, R4, R8_12, R8_11, R8_10, R8_9, R8_8, R8_7, R8_6, R8_5, R8_4, R8_3, R8_2, R8",0603,36,10k,
"R5_12, R5_11, R5_10, R5_9, R5_8, R5_7, R5_6, R5_5, R5_4, R5_3, R5_2, R5",0603,12,5k49,
"R6_12, R6_11, R6_10, R6_9, R6_8, R6_7, R6_6, R6_5, R6_4, R6_3, R6_2, R6",0603,12,100R,
"R7_12, R7_11, R7_10, R7_9, R7_8, R7_7, R7_6, R7_5, R7_4, R7_3, R7_2, R7",0603,12,100k,
"U1_12, U1_11, U1_10, U1_9, U1_8, U1_7, U1_6, U1_5, U1_4, U1_3, U1_2, U1",WSON-8-1EP_3x3mm_P0.5mm_EP1.45x2.4mm_ThermalVias,12,INA826AIDRGR,
